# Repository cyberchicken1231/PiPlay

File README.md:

# PiPlay
PiPlay is a Raspberry Pi Zero 2W-based Game Boy, with full RetroPie capabilities. It can play any Retropie-supported game, as long as it doesn't require joysticks. 
# Bill of Materials
~12 6x6mm pushbuttons
~1 Raspberry Pi Zero 2W
~1 Adafruit 1000C Li-ion battery charger
~1 DPI or HDMI 3.5-inch screen
~1 copy of the PCB
~1 Li-ion battery with the correct header for the charger
~Tools for assembly: 
~1 soldering iron
~1 spool of solder
~1 3d printer
~1 spool of filament
# Setup the Pi
I will post this section when I get to build the project, most likely in a couple of weeks.
# To build:
The Gerber files are in the ZIP file piplay_gbr.zip. Load this ZIP into either:
~A PCB manufacturer
~Your PCB manufacturing setup, if you have one.
While you wait for that, you can go ahead and purchase the parts listed in the Bill of Materials.
Once you have all of the parts, assemble as follows:
1. Solder the buttons to the PCB. Note that the L and R buttons go on the back of the board(L and R are the ones on the same line. L is under the Pi, and R is under nothing, but parallel to L. These will be the shoulder buttons, but on the back instead of up top.
2. Solder the battery charger to the board. Solder the USB-A port to the charger.
3. Solder the Pi to the board, with the Micro-SD card in the slot already. BE SURE NOT TO PLUG THE PI IN BACKWARDS!!!!!
4. Attach the screen to the board. Run the HDMI cable to the Pi. You may have to run it along the outer edge, but you shouldn't have to.
5. Plug in and attach the battery to the board. BE SURE NOT TO PLUG IT IN BACKWARDS!!!!!
7. Plug in. If all went well, it should turn on. You can now either use it or turn on the screensaver and let it charge.
# Use
Load up ROMS of your choice, following the guide that RetroPie has put on their docs. Play games.

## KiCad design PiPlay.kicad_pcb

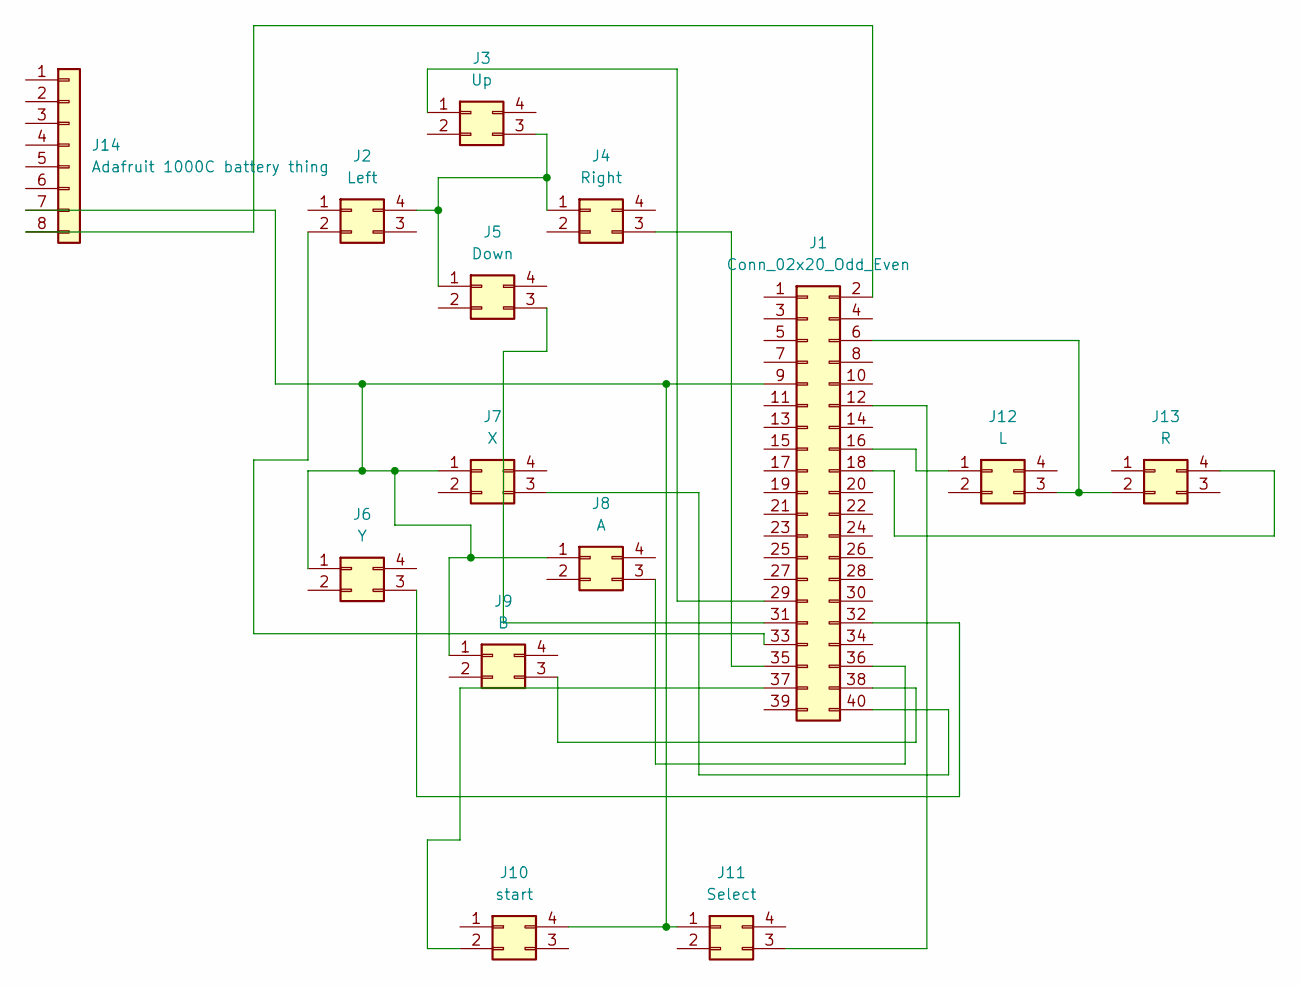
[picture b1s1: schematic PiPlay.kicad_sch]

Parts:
J1: Conn_02x20_Odd_Even; PinHeader_2x20_P2.54mm_Vertical
J2: Left; PinHeader_2x02_P2.54mm_Vertical
J3: Up; PinHeader_2x02_P2.54mm_Vertical
J4: Right; PinHeader_2x02_P2.54mm_Vertical
J5: Down; PinHeader_2x02_P2.54mm_Vertical
J6: Y; PinHeader_2x02_P2.54mm_Vertical
J7: X; PinHeader_2x02_P2.54mm_Vertical
J8: A; PinHeader_2x02_P2.54mm_Vertical
J9: B; PinHeader_2x02_P2.54mm_Vertical
J10: start; PinHeader_2x02_P2.54mm_Vertical
J11: Select; PinHeader_2x02_P2.54mm_Vertical
J12: L; PinHeader_2x02_P2.54mm_Vertical
J13: R; PinHeader_2x02_P2.54mm_Vertical
J14: Adafruit 1000C battery thing; PinHeader_1x08_P2.54mm_Vertical

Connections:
unnamed: J1.2, J14.8
unnamed: J1.6, J12.3, J13.2
unnamed: J1.9, J6.1, J7.1, J8.1, J9.1, J10.4, J11.1, J14.7
unnamed: J1.12, J11.3
unnamed: J1.16, J12.1
unnamed: J1.18, J13.4
unnamed: J1.29, J3.1
unnamed: J1.31, J5.3
unnamed: J1.32, J6.3
unnamed: J1.33, J2.2
unnamed: J1.35, J4.3
unnamed: J1.36, J8.3
unnamed: J1.37, J10.2
unnamed: J1.38, J9.3
unnamed: J1.40, J7.3
unnamed: J2.4, J3.3, J4.1, J5.1

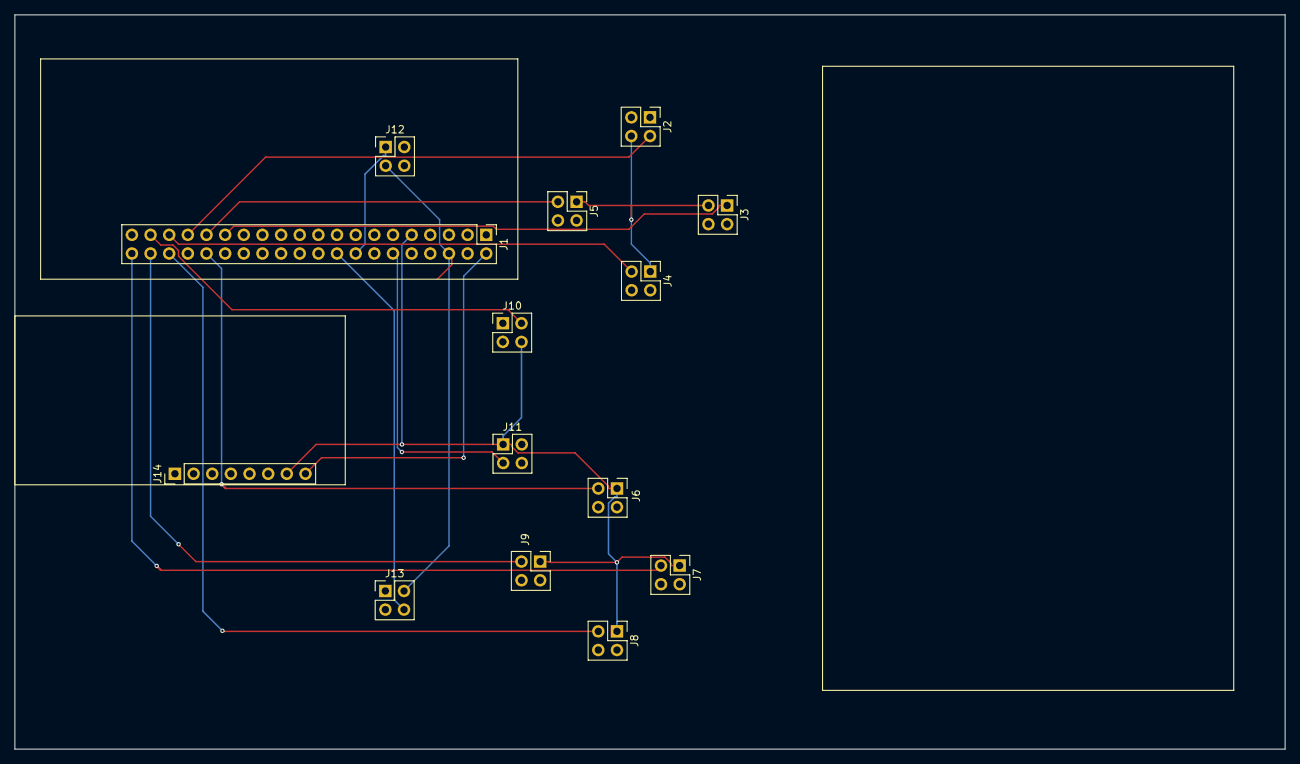
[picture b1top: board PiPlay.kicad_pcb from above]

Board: 2 copper layers, 173.0 x 100.0 mm, 14 parts (0 on the bottom side), 16 nets.

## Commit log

2025-10-14 Add files via upload
    Add KiCad files and Gerber files
2025-10-18 Create bom.csv with component details
    Added a bill of materials (BOM) for the project.
